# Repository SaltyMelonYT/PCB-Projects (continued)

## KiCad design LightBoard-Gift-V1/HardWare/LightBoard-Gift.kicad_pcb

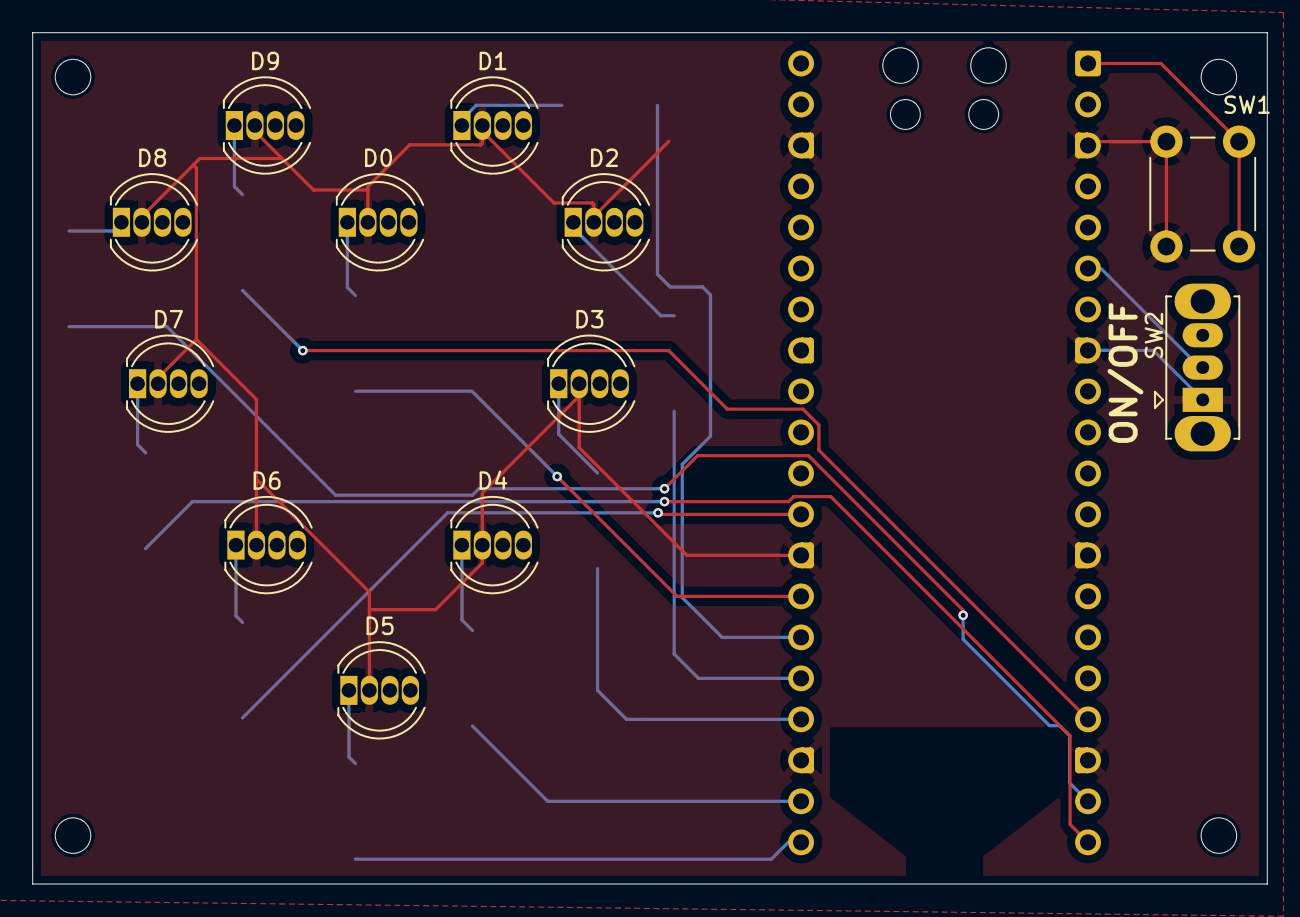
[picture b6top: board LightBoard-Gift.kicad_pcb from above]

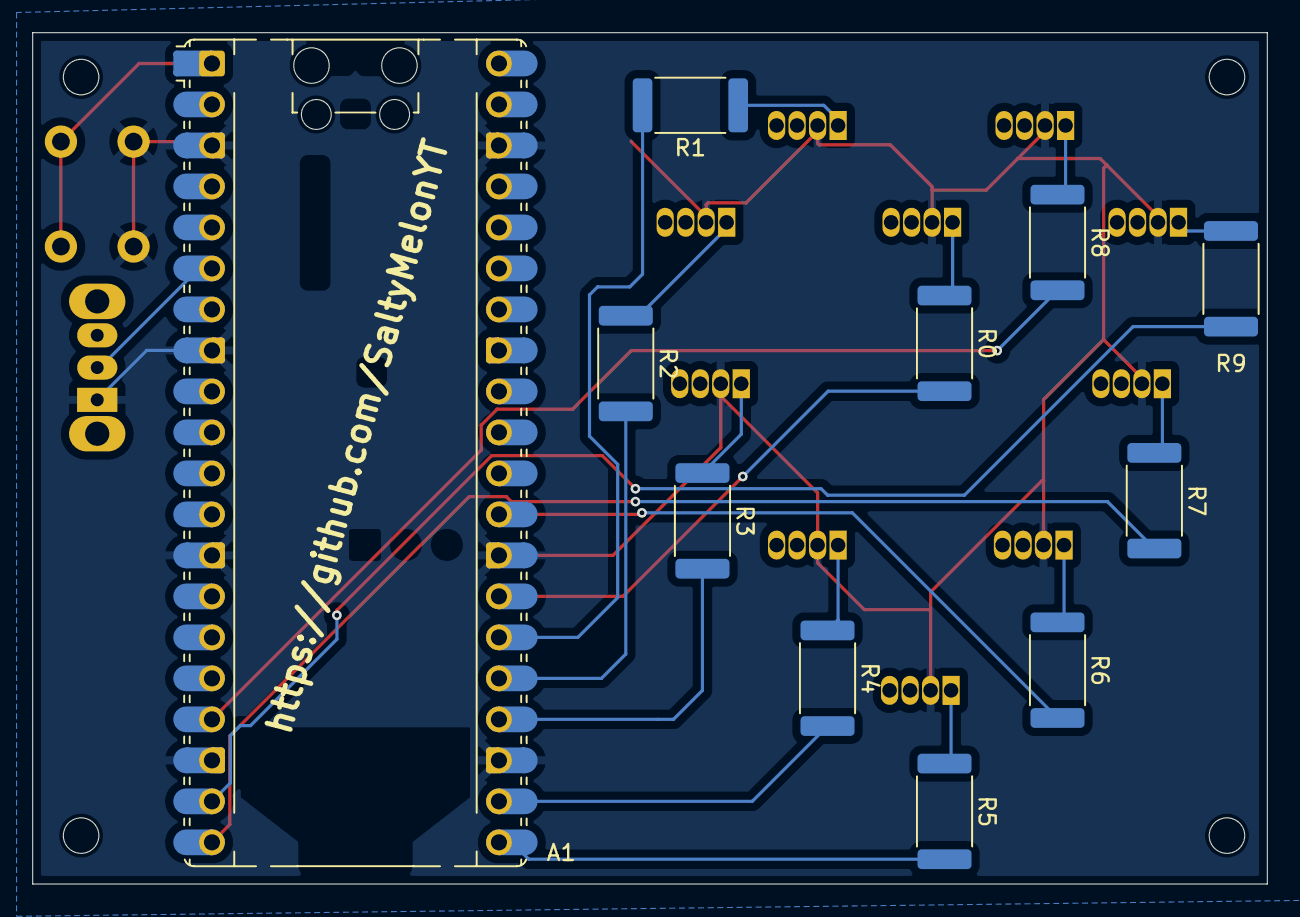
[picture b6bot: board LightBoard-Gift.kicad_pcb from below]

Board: 2 copper layers, 76.5 x 52.8 mm, 27 parts (11 on the bottom side), 23 nets.

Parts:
A1: RaspberryPi_Pico; RaspberryPi_Pico_Common_Unspecified
D0, D1, D2, D3, D4, D5, D6, D7, D8, D9: LED_RKGB; LED_D5.0mm-4_RGB
H1, H2, H3, H4: MountingHole; MountingHole_2.2mm_M2
R0, R1, R2, R4, R5, R6, R7, R8, R9: 560Ohm; R_2512_6332Metric
R3: R_Small; R_2512_6332Metric
SW1: MODE_SELECT; SW_PUSH_6mm_H4.3mm
SW2: SWITCH; SW_Slide_SPDT_Straight_CK_OS102011MS2Q

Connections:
GND: A1.3 (GND), A1.8 (GND), A1.13 (GND), A1.18 (GND), A1.23 (GND), A1.28 (GND), A1.38 (GND), D0.2 (K), D1.2 (K), D2.2 (K), D3.2 (K), D4.2 (K), D5.2 (K), D6.2 (K), D7.2 (K), D8.2 (K), D9.2 (K), SW1.2, SW2.1
unnamed: A1.1 (GPIO0), SW1.1
unnamed: A1.6 (GPIO4), SW2.2
unnamed: D0.1 (RA), R0.1
unnamed: D1.1 (RA), R1.1
unnamed: D2.1 (RA), R2.1
unnamed: D3.1 (RA), R3.1
unnamed: D4.1 (RA), R4.1
unnamed: D5.1 (RA), R5.1
unnamed: D6.1 (RA), R6.1
unnamed: D7.1 (RA), R7.1
unnamed: D8.1 (RA), R9.1
unnamed: D9.1 (RA), R8.1
RED0: A1.27 (GPIO21), R0.2
RED1: A1.26 (GPIO20), R1.2
RED2: A1.25 (GPIO19), R2.2
RED3: A1.24 (GPIO18), R3.2
RED4: A1.22 (GPIO17), R4.2
RED5: A1.21 (GPIO16), R5.2
RED6: A1.29 (GPIO22), R6.2
RED7: A1.20 (GPIO15), R7.2
RED8: A1.19 (GPIO14), R9.2
RED9: A1.17 (GPIO13), R8.2
